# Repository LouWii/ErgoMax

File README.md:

# ErgoMax

The ErgoMax is a split ergonomic keyboard.

It is based on the ErgoDox, a popular split ergonomic keyboard ([learn more](https://www.ergodox.io/)). 

Its main features/differences are:

* extra top row for F1-F12 keys
* hot-swappable switches
* uses 2 ProMicro controllers (one for each side)
* QMK firmware
* 2 versions of the PCBs:
    * a reversible left+right combined
    * 2 separate PCBs, one for each side
* either side can be master/slave
* both sides can be master (both sides need to be connected via USB in that case), allow for a 1 side only setup
* 2 input pins left (perfect for a rotary encoder!)
* **DIY friendly**: it's really super easy to assemble yourself. The hardest part is probably the ProMicro. But it's still very accessible for beginners.
* multi layer acrylic case

## Layout

While a lot of mechanical keyboard users seem to prefer simplistic, minimal keyboards, the ErgoMax goes the opposite way.

The layout is the same as the ErgoDox, **with an extra top row** for *F1* to *F12* keys, adding more room for activities.

Here's an example:

## Hotswap - change switches whenever you want

The keyboard PCB has been designed to use **Kailh MX hotswap sockets**. You won't be able to solder the switches directly on the PCBs, you **must** use Kaihl MX sockets.

Switches will plug into the sockets, meaning no solder required for them, and most importantly, meaning that you can remove them and change them easily (hence the *hotswap*...).

## Controller

Each side of the keyboard is controlled via a ProMicro, which is a cheap, small Arduino compatible board running on an ATmega32u4.

The 2 sides can be connected via a 3.5mm jack, just like the original ErgoDox. However, as the 2 sides possess their own ProMicro, that means they can also be working totally independently if needed.

There are 2 pins free on each of the ProMicros, which can be used for whatever you want. I believe it would be possible to drive a RGB strip from it, since it requires only 1 drive pin (you would need to get GND and +5V from somewhere on the PCB). I was able to use both pins to add a rotary encoder.

### Jack connector

I tried to use the same 3.5mm TRRS jack socket as the original ErgoDox, which is a *CP-43514*. But it's not super common, so I changed it for a *PJ320A* (same as *MJ-4PP-9*).

### Firmware

Check the [guides](Guide/README.md)

## Third Party Libraries

We are using several libraries in this project.

* keyboard_parts.pretty [https://github.com/colemarkham/keyboard_parts.pretty](https://github.com/colemarkham/keyboard_parts.pretty) - The Kailh hotswap socket footprint is taken from this project, and has been slightly modified. The 2U stabilizer footprint is from this library as well.
* ProMicroKiCad [https://github.com/Biacco42/ProMicroKiCad](https://github.com/Biacco42/ProMicroKiCad) - The schema and footprint for the ProMicro
* Keebio-Parts.pretty [https://github.com/keebio/Keebio-Parts.pretty](https://github.com/keebio/Keebio-Parts.pretty) - Footprints for the diodes, the PJ320A jack connector, and resistors

### 3D models

Kicad can generate nice 3D previews of PCBs and their components.

As we're using components that are not included in KiCad 3d templates, you'll need to add the next models into your KiCad template folder. On Windows, it's `C:\Users\YOURNAME\kicad\template`, on OSX it's `/Users/YOURNAME/kicad/template`. If the folder doesn't exist, create it.

The 3D models of the hotswap sockets can be found there: [https://github.com/qmk/qmk_hardware](https://github.com/qmk/qmk_hardware). Copy `kailh_socket_mx.stp` into your KiCad template folder.

I couldn't find a 3D model for the PJ320A jack connector. The closest I found is this [https://www.cui.com/product/resource/3dmodel/sj2-3574a-smt-tr](https://www.cui.com/product/resource/3dmodel/sj2-3574a-smt-tr), which gives a good preview of a real PJ320A. Copy `CUI_SJ2-3574A-SMT-TR.step` into your KiCad template folder.

I modified this MX Switch 3D model [https://grabcad.com/library/cherry-mx-switches-mx-1](https://grabcad.com/library/cherry-mx-switches-mx-1) and included it in the `libs/3dmodels` folder of the project as `MX-clean-ergomax.step`. 

I also modified a 2U stabilizer model that I found there [https://grabcad.com/library/cherry-mx-stabilizer-mx-1](https://grabcad.com/library/cherry-mx-stabilizer-mx-1). The file is also included in the `libs/3dmodels` folder of the project as `Stabilizer-closed-ergomax.step`.

I once again modified a ProMicro 3D model [https://grabcad.com/library/arduino-pro-micro-1](https://grabcad.com/library/arduino-pro-micro-1). The file is called `Pro-micro-clean-ergomax.step` and is stored in `libs/3dmodels`.

## Print the PCBs

Here are some manufacturers that can print PCBs for you. They are not in any particular order and I don't have any partnership of any sort either.

* [https://pcbshopper.com/ - price comparison](https://pcbshopper.com/) 
* [https://jlcpcb.com/](https://jlcpcb.com/)
* [https://www.pcbway.com/](https://www.pcbway.com/)
* [https://oshpark.com/](https://oshpark.com/)
* [https://www.pcbcart.com/](https://www.pcbcart.com/)
* [https://www.7pcb.ca/](https://www.7pcb.ca/pcb-fabrication/)
* [https://www.4pcb.com/](https://www.4pcb.com/)
* [https://www.pcbgogo.com/](https://www.pcbgogo.com/)
* [https://dirtypcbs.com/](https://dirtypcbs.com/)

## Assembly

Check the [guides](Guide/README.md)

## Case

[See Case readme](./Case/)

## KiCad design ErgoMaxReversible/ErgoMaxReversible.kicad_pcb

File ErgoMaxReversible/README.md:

# ErgoMax Reversible

As its name suggests, the reversible PCB can be used for either the left side or right side. 

## PCB

Render from KiCad.

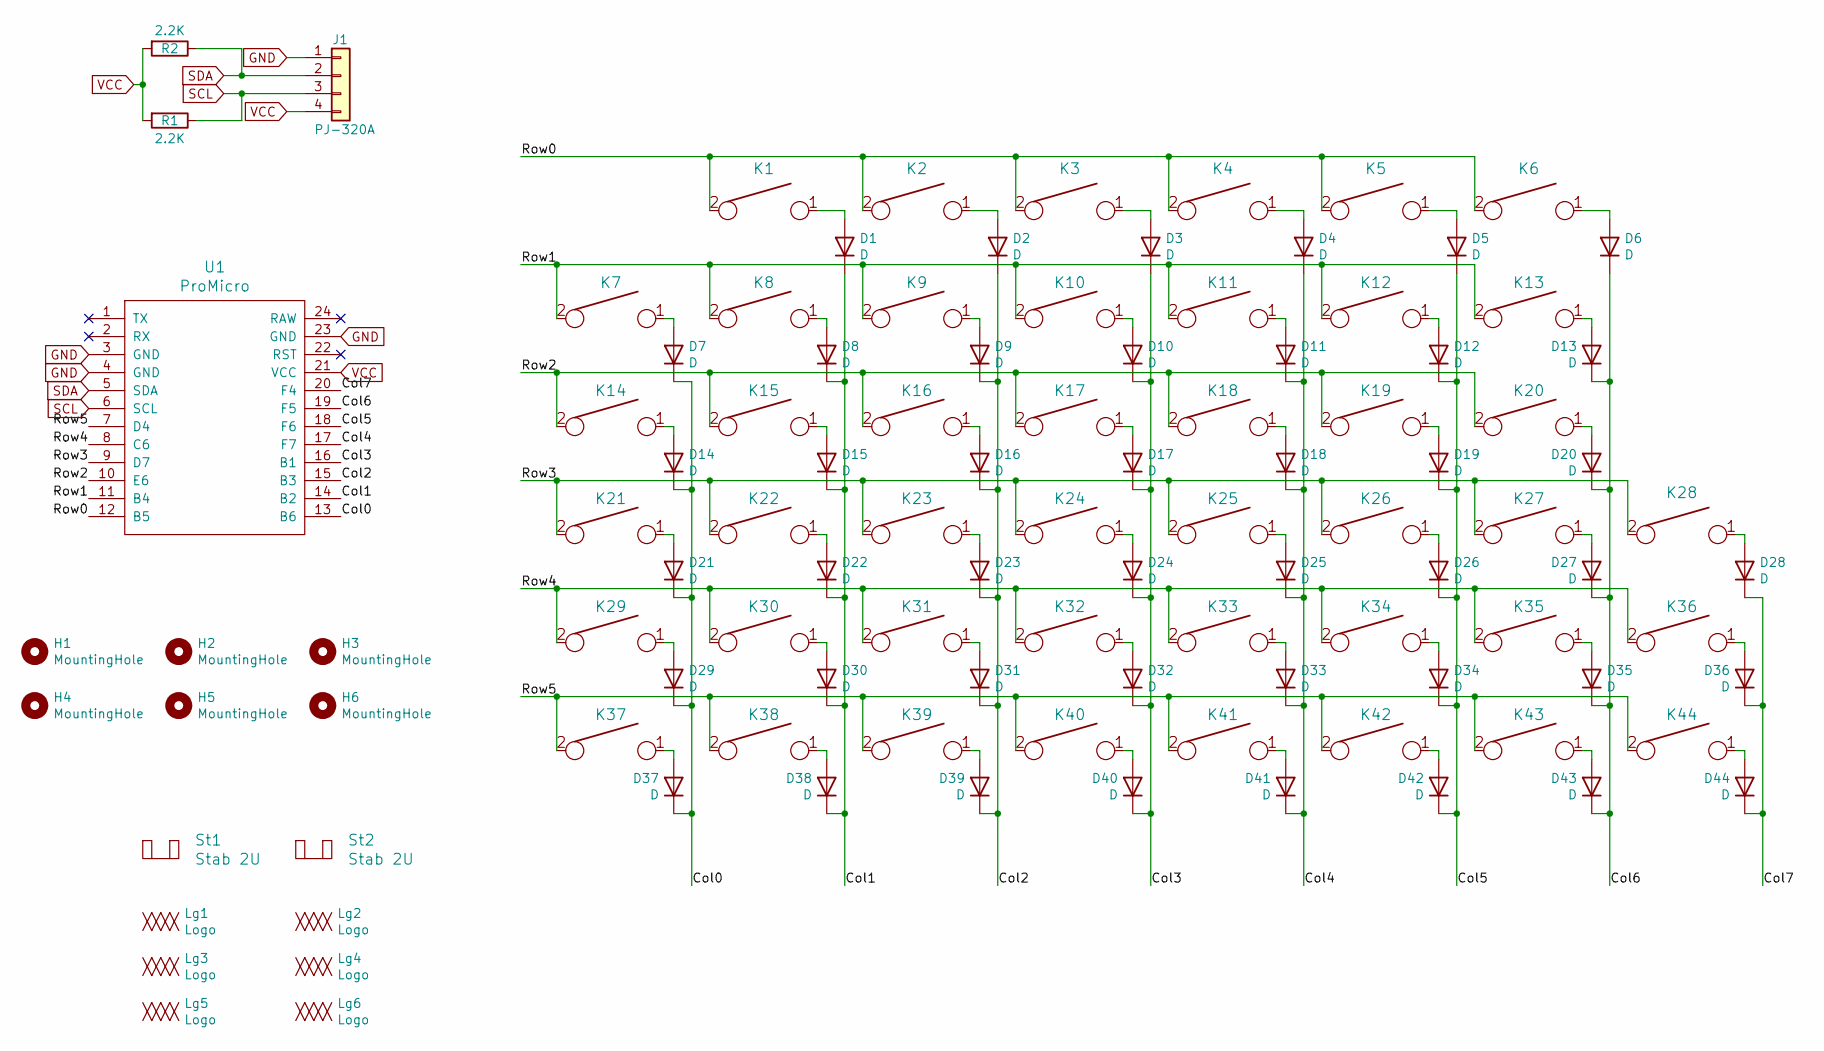
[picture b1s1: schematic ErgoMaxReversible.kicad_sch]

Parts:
D1, D2, D3, D4, D5, D6, D7, D8, D9, D10, D11, D12, D13, D14, D15, D16, D17, D18, D19, D20, D21, D22, D23, D24, D25, D26, D27, D28, D29, D30, D31, D32, D33, D34, D35, D36, D37, D38, D39, D40, D41, D42, D43, D44: D; Diode_Long_Reversible-No3dModel
H1, H2, H3, H4, H5, H6: MountingHole; MountingHole_6mm
J1: PJ-320A; TRRS-PJ-320A-dual
K1, K2, K3, K4, K5, K6, K7, K8, K9, K10, K11, K12, K13, K14, K15, K16, K17, K18, K19, K20, K21, K22, K23, K24, K25, K26, K27, K28, K29, K30, K31, K32, K33, K34, K35, K36, K37, K38, K39, K40, K41, K42, K43, K44: KEYSW; Kailh_socket_MX_reversible
Lg1, Lg3: Logo; LouWii-logo
Lg2, Lg4: Logo; ErgoMax-logo
Lg5: Logo; LeftSideText
Lg6: Logo; RightSideText
R1, R2: 2.2K; Resistor
St1, St2: Stab 2U; Mx_Stab_200
U1: ProMicro; ProMicroReversible

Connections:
/Col0: D7.1 (K), D14.1 (K), D21.1 (K), D29.1 (K), D37.1 (K), U1.13 (B6)
/Col1: D1.1 (K), D8.1 (K), D15.1 (K), D22.1 (K), D30.1 (K), D38.1 (K), U1.14 (B2)
/Col2: D2.1 (K), D9.1 (K), D16.1 (K), D23.1 (K), D31.1 (K), D39.1 (K), U1.15 (B3)
/Col3: D3.1 (K), D10.1 (K), D17.1 (K), D24.1 (K), D32.1 (K), D40.1 (K), U1.16 (B1)
/Col4: D4.1 (K), D11.1 (K), D18.1 (K), D25.1 (K), D33.1 (K), D41.1 (K), U1.17 (F7)
/Col5: D5.1 (K), D12.1 (K), D19.1 (K), D26.1 (K), D34.1 (K), D42.1 (K), U1.18 (F6)
/Col6: D6.1 (K), D13.1 (K), D20.1 (K), D27.1 (K), D35.1 (K), D43.1 (K), U1.19 (F5)
/Col7: D28.1 (K), D36.1 (K), D44.1 (K), U1.20 (F4)
/Row0: K1.2, K2.2, K3.2, K4.2, K5.2, K6.2, U1.12 (B5)
/Row1: K7.2, K8.2, K9.2, K10.2, K11.2, K12.2, K13.2, U1.11 (B4)
/Row2: K14.2, K15.2, K16.2, K17.2, K18.2, K19.2, K20.2, U1.10 (E6)
/Row3: K21.2, K22.2, K23.2, K24.2, K25.2, K26.2, K27.2, K28.2, U1.9 (D7)
/Row4: K29.2, K30.2, K31.2, K32.2, K33.2, K34.2, K35.2, K36.2, U1.8 (C6)
/Row5: K37.2, K38.2, K39.2, K40.2, K41.2, K42.2, K43.2, K44.2, U1.7 (D4)
GND: J1.1, U1.3 (GND), U1.4 (GND), U1.23 (GND)
unnamed: D1.2 (A), K1.1
unnamed: D2.2 (A), K2.1
unnamed: D3.2 (A), K3.1
unnamed: D4.2 (A), K4.1
unnamed: D5.2 (A), K5.1
unnamed: D6.2 (A), K6.1
unnamed: D7.2 (A), K7.1
unnamed: D8.2 (A), K8.1
unnamed: D9.2 (A), K9.1
unnamed: D10.2 (A), K10.1
unnamed: D11.2 (A), K11.1
unnamed: D12.2 (A), K12.1
unnamed: D13.2 (A), K13.1
unnamed: D14.2 (A), K14.1
unnamed: D15.2 (A), K15.1
unnamed: D16.2 (A), K16.1
unnamed: D17.2 (A), K17.1
unnamed: D18.2 (A), K18.1
unnamed: D19.2 (A), K19.1
unnamed: D20.2 (A), K20.1
unnamed: D21.2 (A), K21.1
unnamed: D22.2 (A), K22.1
unnamed: D23.2 (A), K23.1
unnamed: D24.2 (A), K24.1
unnamed: D25.2 (A), K25.1
unnamed: D26.2 (A), K26.1
unnamed: D27.2 (A), K27.1
unnamed: D28.2 (A), K28.1
unnamed: D29.2 (A), K29.1
unnamed: D30.2 (A), K30.1
unnamed: D31.2 (A), K31.1
unnamed: D32.2 (A), K32.1
unnamed: D33.2 (A), K33.1
unnamed: D34.2 (A), K34.1
unnamed: D35.2 (A), K35.1
unnamed: D36.2 (A), K36.1
unnamed: D37.2 (A), K37.1
unnamed: D38.2 (A), K38.1
unnamed: D39.2 (A), K39.1
unnamed: D40.2 (A), K40.1
unnamed: D41.2 (A), K41.1
unnamed: D42.2 (A), K42.1
unnamed: D43.2 (A), K43.1
unnamed: D44.2 (A), K44.1
SCL: J1.3, R1.1, U1.6 (SCL)
SDA: J1.2, R2.1, U1.5 (SDA)
VCC: J1.4, R1.2, R2.2, U1.21 (VCC)

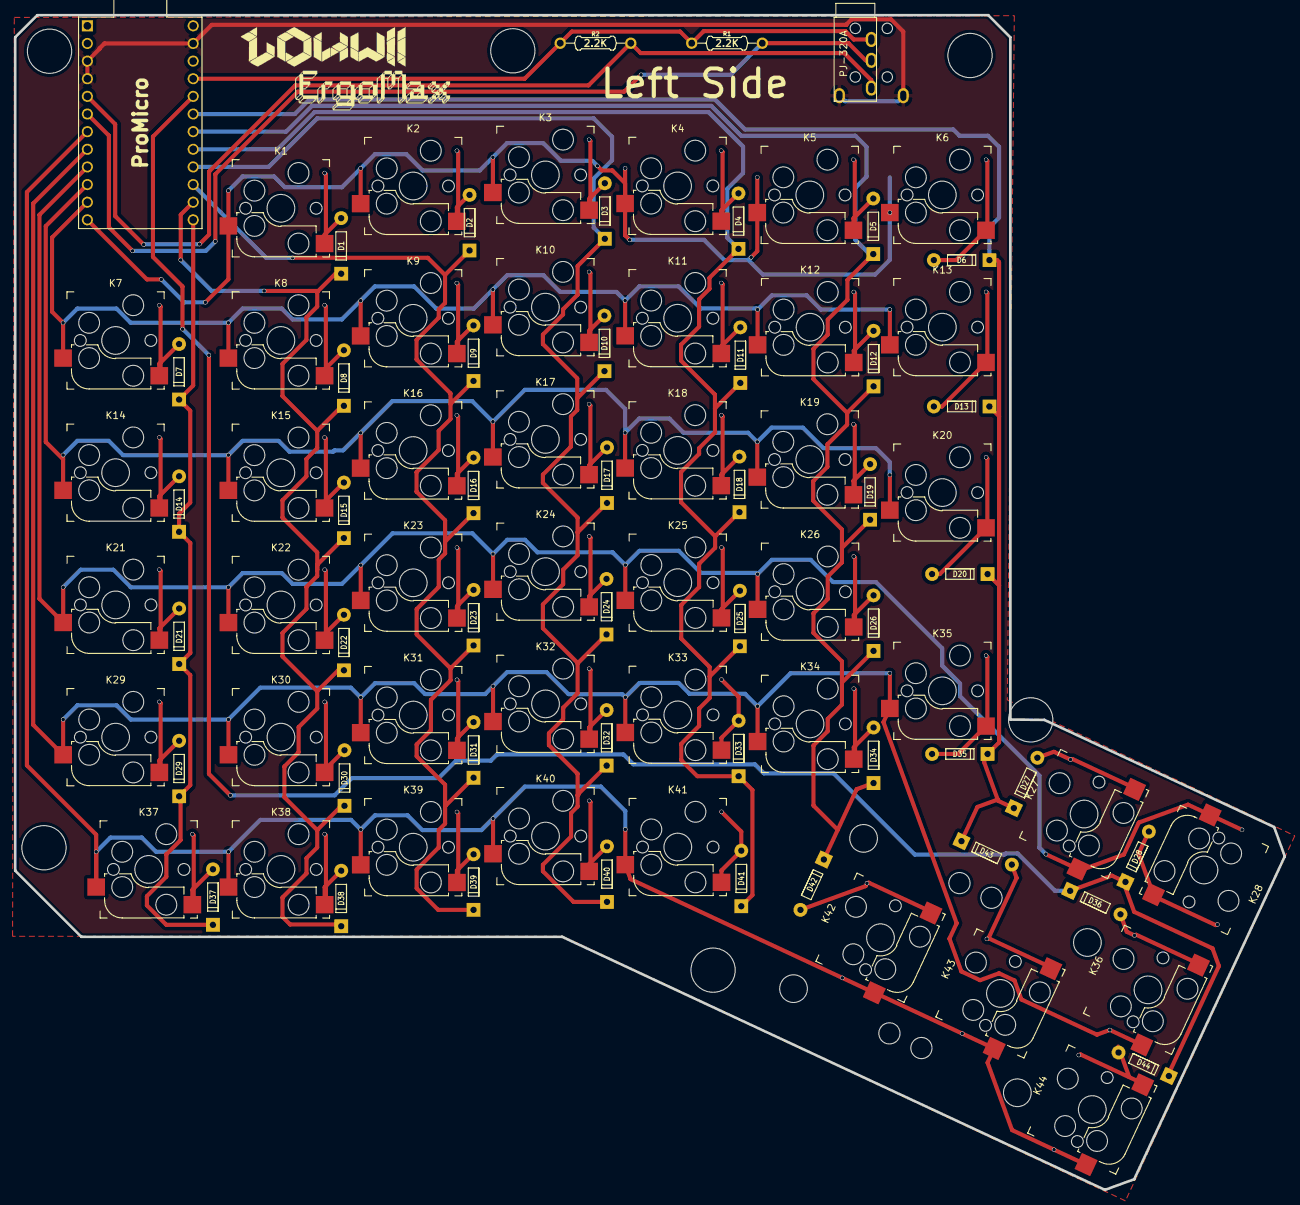
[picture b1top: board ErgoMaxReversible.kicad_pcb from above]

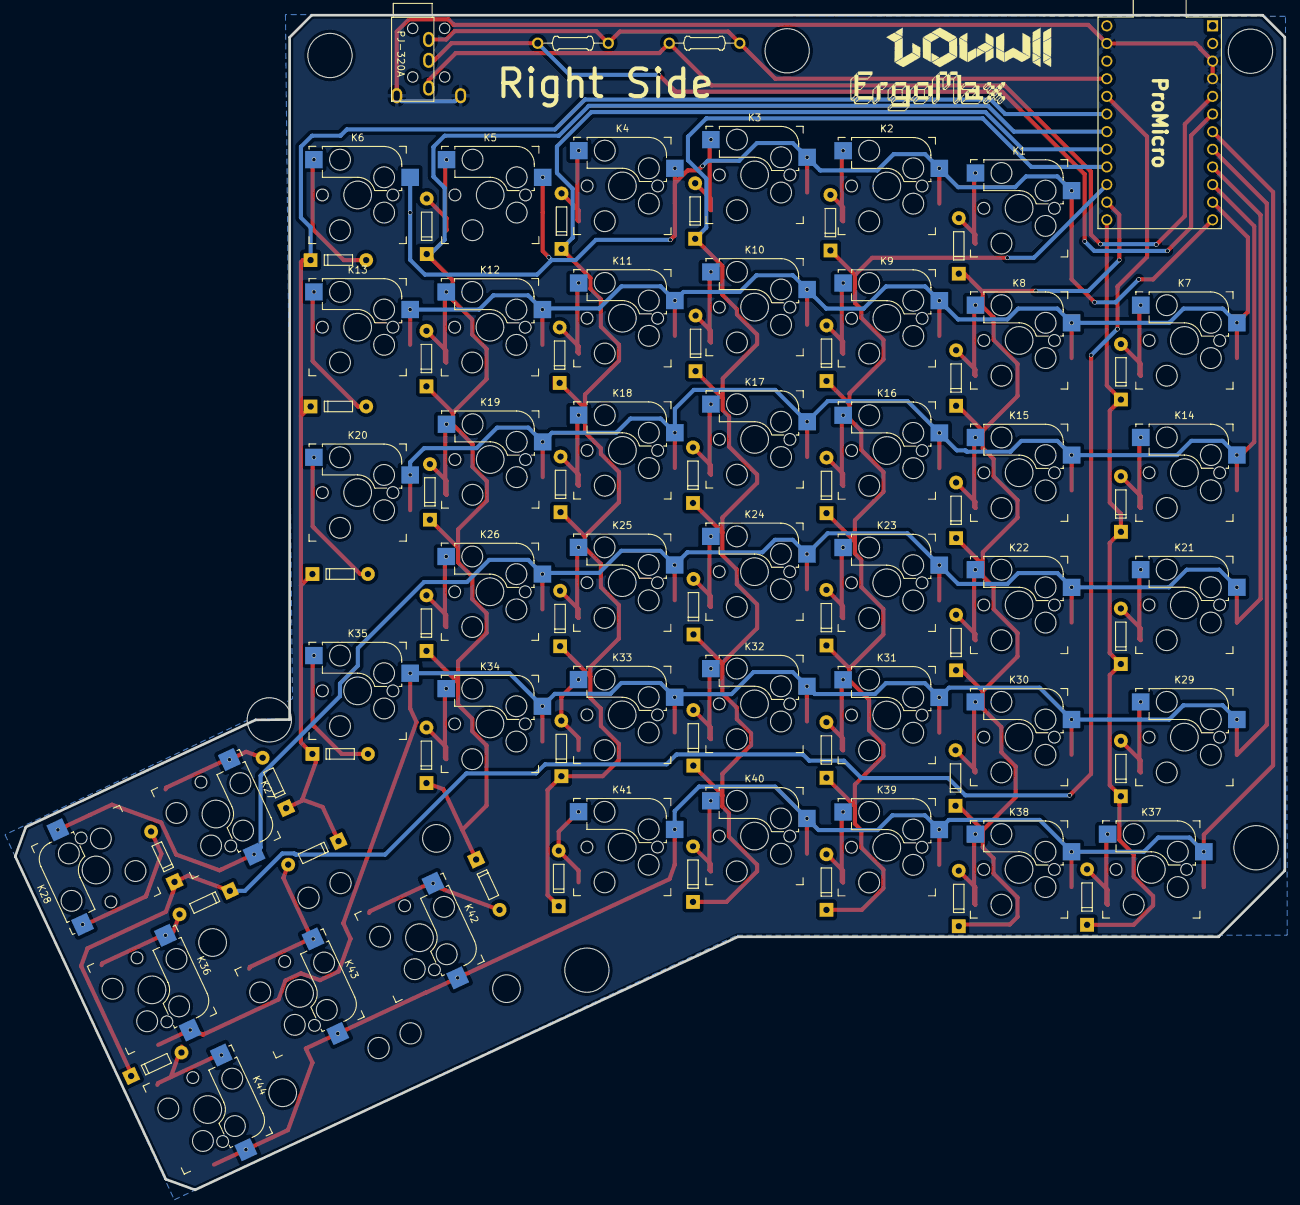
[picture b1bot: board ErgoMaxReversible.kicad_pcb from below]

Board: 2 copper layers, 182.8 x 169.2 mm, 106 parts (2 on the bottom side), 62 nets.

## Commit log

2018-11-10 first commit, schematics done, PCB WIP
2018-11-11 WIP: placing switch sockets on PCB
2018-11-12 WIP align even more switch sockets, line 4
2018-11-12 WIP: PCB - last row set, side keys needed
2018-11-13 WIP PCB place 2 right side 1.5u key sockets
2018-11-13 WIP PCB - place left 1.5u switch sockets
2018-11-13 WIP PCB: fix spacing for the 2 1.5u keys on right side
2018-11-13 WIP PCB: place thumb switch sockets
2018-11-13 WIP PCB - rotate thumb 2u keys to be oriented properly for stabs
2018-11-14 WIP PCB - add 2 cutouts
2018-11-14 WIP PCB - make rough cutout so Kicad doesn't complain anymore, add 2 mounting holes
2018-11-14 WIP PCB - fix placement of thumb switch sockets
2018-11-14 WIP PCB - add more mouting holes based on ErgoDox
2018-11-14 WIP PCB - make proper cutout for the top
2018-11-14 WIP PCB - add 2 zones and start routing
2018-11-14 WIP PCB - more routing
2018-11-15 WIP PCB - update diodes footprints to something more accurate, displayed in the proper direction
2018-11-15 WIP PCB - replace jack connector in schematics and PCB to something that actually works properly
2018-11-15 Add stuff in README
2018-11-16 Change Jack 3.5 connector to PJ-320A model 4 pins
2018-11-16 create most of the routes for switches - rough, needs refining
2018-11-17 Re-work pro mini pinout for better wiring on PCB and finish PCB wiring
2018-11-17 add bridges so copper layers fill up most of the PCB
2018-11-17 minor text adjustments on PCB
2018-11-17 fix misaligned PCB cut limit, add gerbers files
2018-11-17 refactoring to add mounting holes
2018-11-17 change small resistor placement on PCB and update gerber files
2018-11-17 rename ErgoMax left ro right as it's... for the right hand
2018-11-17 add a 2u stab for thumb key - WIP
2018-11-17 add second stab to thumb key
2018-11-18 modify library for MX Kailh sockets; add mounting holes in schema for PCB
2018-11-19 add missing stabs in schema, add them back in PCB
2018-11-19 replace some labels on PCB for clarity
2018-11-19 rename footprint library to ErgoMax for clarity
2018-11-19 add custom logos in schema and PCB (added them in libs)
2018-11-19 move libs to main folder
2018-11-19 add ErgoMax left part; PCB started with switches, holes, logos, stabs placed
2018-11-19 move last components to other side of the PCB
2018-11-19 update readmes
2018-11-20 move diodes to other side of switches; add rough wiring for rows
2018-11-20 cleanup diodes positions
2018-11-20 add more wiring - wiring columns is going to cause some problems
2018-11-21 Clean up some wiring and move jack connector to the right side!
2018-11-21 add a reversible version with hot swap sockets - PCB WIP
2018-11-21 more wiring on reversible PCB
2018-11-21 wiring again for reversible pcb
2018-11-22 add 3D models in footprints properties
2018-11-22 add details for jack connector 3d model in readme
2018-11-22 add a cleaned MX switch 3d model and use it in one spot in the PCB
2018-11-22 update switch 3d model name in PCB (was using the old name)
2018-11-23 add stablizer model and use it on right PCB
2018-11-23 improve ErgoMax right PCB
2018-11-23 make diodes appear on PCB 3d model for right pcb
2018-11-23 add pro micro 3d model and use it on right PCB
2018-11-23 update readme for ErgoMaxRight
2018-11-23 improve wiring on reversible pcb
2018-11-23 update gerbers files for ErgoMax right PCB
2018-11-24 update readme links and path for OSX kicad templates
2018-11-24 finish and improve reversible PCB
2018-11-24 more improvements on reversible pcb
2018-11-24 update jack connector to be reversible; add logos on back of the pcb - reversible pcb
2018-11-24 add reversible gerbers files
2018-11-25 finish left PCB and add 3d models
2018-11-25 add readme and screenshots for the left pcb
2018-11-25 add gerbers for left pcb
2018-11-26 add list of pcb services sites in readme
2018-11-26 add footprints for reversible diode with and without 3d model and use it on reversible pcb
2018-11-26 improve footprints on reversible PCB and add sides markings
2018-11-26 add readme for reversible PCB
2018-11-27 add add values for main keys on PCB
2018-11-29 start doc about assembly
2018-12-01 move logos to front side of left and right PCB, add left/right writings
2018-12-05 Re-structure the README
2018-12-06 add assembly doc link in README
2018-12-09 add firmware doc
2018-12-11 update readme and assembly
2018-12-12 update firmware doc
2018-12-13 add redox to firmware doc
2018-12-13 update firmware doc with more links
2018-12-23 add config file for KFB and add note in FIRMWARE.md
2019-01-10 fix typo in Kailh
2019-01-23 add CAD models for the left case - WIP
2019-01-23 add proper export file for ErgoMax left case
2019-01-23 add PCB 3d model (export from kicad)
2019-01-23 add step file for left case
2019-02-15 update CAD for cnc case for Ergomax left side
2019-02-15 update eeschema with infos and add PDF file for quick view of the schematics
2019-02-15 update gerbers for ErgoMax right (not sure they were the last version)
2019-02-16 change resistors side and add 3D models on ErgoMax left
2019-02-16 add jack connector 3d model to ErgoMax elft
2019-02-16 change resistors side on ErgoMax right and fix 3d models
2019-02-16 update 2d renders in ErgoMax left/right readmes
2019-02-25 add base files for acrylic case for ergo left
2019-02-25 remove duplicate files
2019-02-25 continue adding switch cuts on left plate
2019-02-26 finish switch cutout on left plate
2019-02-26 start external cut on left plate
2019-02-26 left plate almost complete - 2 holes missing
2019-02-28 finish up acrylic plate
2019-02-28 cleanup plate and add bottom layer
2019-02-28 add rough start for layer 4
2019-03-01 add complete layer 4
2019-03-01 add layer 2
2019-03-02 add layer 1, add holes for logo in plate and layer 2
2019-03-02 cleanup layers, rename, create files for ponoko
2019-03-14 consolidate acrylic plates
2019-03-14 add CAD for Ponoko manufacturing
2019-03-18 update acrylic designs
2019-06-26 update readmes and guides
2019-08-30 Update Firmware guide
2019-11-14 add layout picture
2020-01-02 Update readme and guide files, add image
2020-01-03 Update license file
2020-01-03 update license again
2023-02-17 Fix ground plane on reversible PCB
2023-04-19 Make reversible PCB use 5 pin hot swap footprint
2023-04-19 Fix last net connection
2023-04-20 Fix net
2023-05-06 Clean up CAD folder
2023-05-06 Update readme internal links
2023-05-08 Final version
2023-06-17 case variant Type C
